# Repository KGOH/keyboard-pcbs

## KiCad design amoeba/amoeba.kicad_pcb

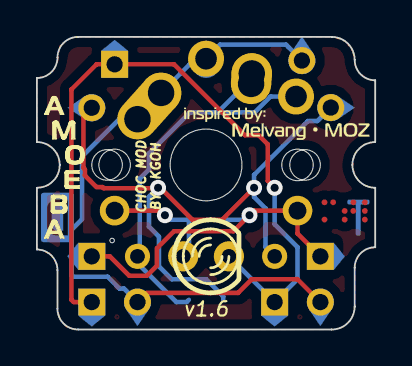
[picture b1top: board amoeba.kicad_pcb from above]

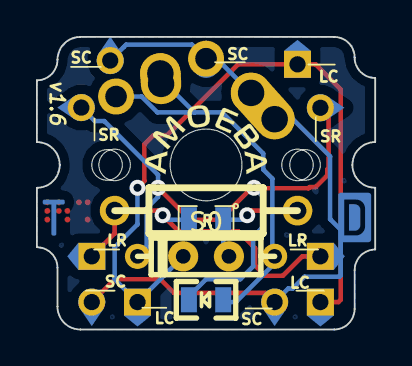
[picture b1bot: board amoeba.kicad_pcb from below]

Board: 2 copper layers, 18.8 x 16.3 mm, 33 parts (15 on the bottom side), 6 nets.

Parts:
D0: DIODE; D3
D1: DIODE; SM0805D
LC0:0, LC0:1, LC0:2: CONN_1; Pad
LED0: LED; LED-3MM
LR0:0, LR0:1: CONN_1; Pad
R0: RESISTOR
R1: RESISTOR; SM0805
S0: MX1A; MX-Alps-Choc-1U-NoLED
SC0:1, SC0:2, SC0:3: CONN_1; Pad
SR0:0, SR0:1: CONN_1; Pad
amoeba-round-rev: G***; amoeba-round-rev
amoeba-vertical: G***; amoeba-vertical
dt-logo-d-rev: G***; dt-logo-d-rev
dt-logo-t-rev: G***; dt-logo-t-rev
labels-melvang-moz: G***; labels-melvang-moz
mtl-braille: G***; mtl-braille
pad-arrow-round: G***; pad-arrow-round
pad-arrow-round#2, pad-arrow-round#3, pad-arrow-round#4, pad-arrow-round#5, pad-arrow-round#6: G***; pad-arrow-round
pad-arrow-square: G***; pad-arrow-square
pad-arrow-square#2, pad-arrow-square#3, pad-arrow-square#4, pad-arrow-square#5: G***; pad-arrow-square

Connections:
/key/LC0: LC0:0.1, LC0:1.1, LC0:2.1, LED0.2
/key/LR0: LR0:0.1, LR0:1.1, R0.2, R1.2
/key/SC0: S0.2, SC0:1.1, SC0:2.1, SC0:3.1
/key/SR0: D0.2, D1.2, SR0:0.1, SR0:1.1
/key/led/N-LR0: LED0.1, R0.1, R1.1
/key/switch/N-SD0: D0.1, D1.1, S0.1

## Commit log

2019-06-30 added amoeba 1.6 w/choc footprint
